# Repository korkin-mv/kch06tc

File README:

KCH06TC

This is a personal project of the controller for the control of the terrarium.

The board was developed from components available to the author, and therefore 
the project should be presented as an introduction and not in any way a 
repetition.

License: MIT.
Copyright (c) 2020 Mihail Korkin <korkin_mv@protonmail.ch>.

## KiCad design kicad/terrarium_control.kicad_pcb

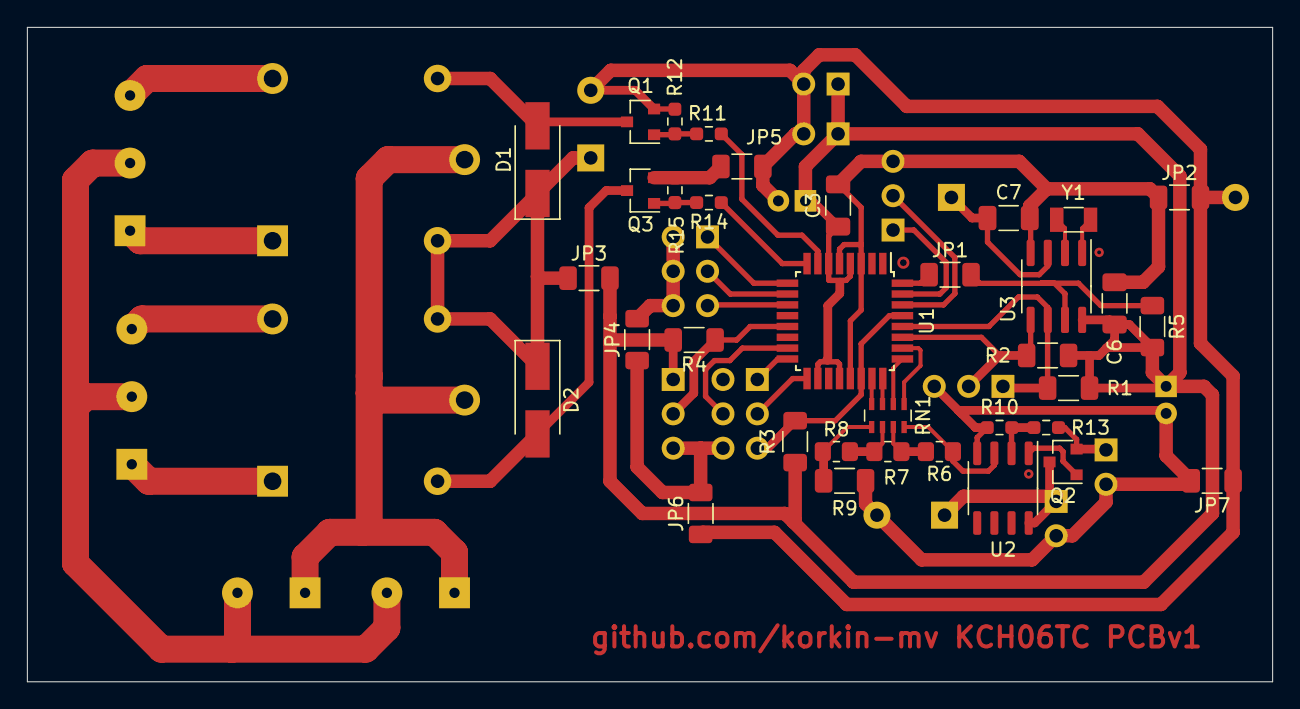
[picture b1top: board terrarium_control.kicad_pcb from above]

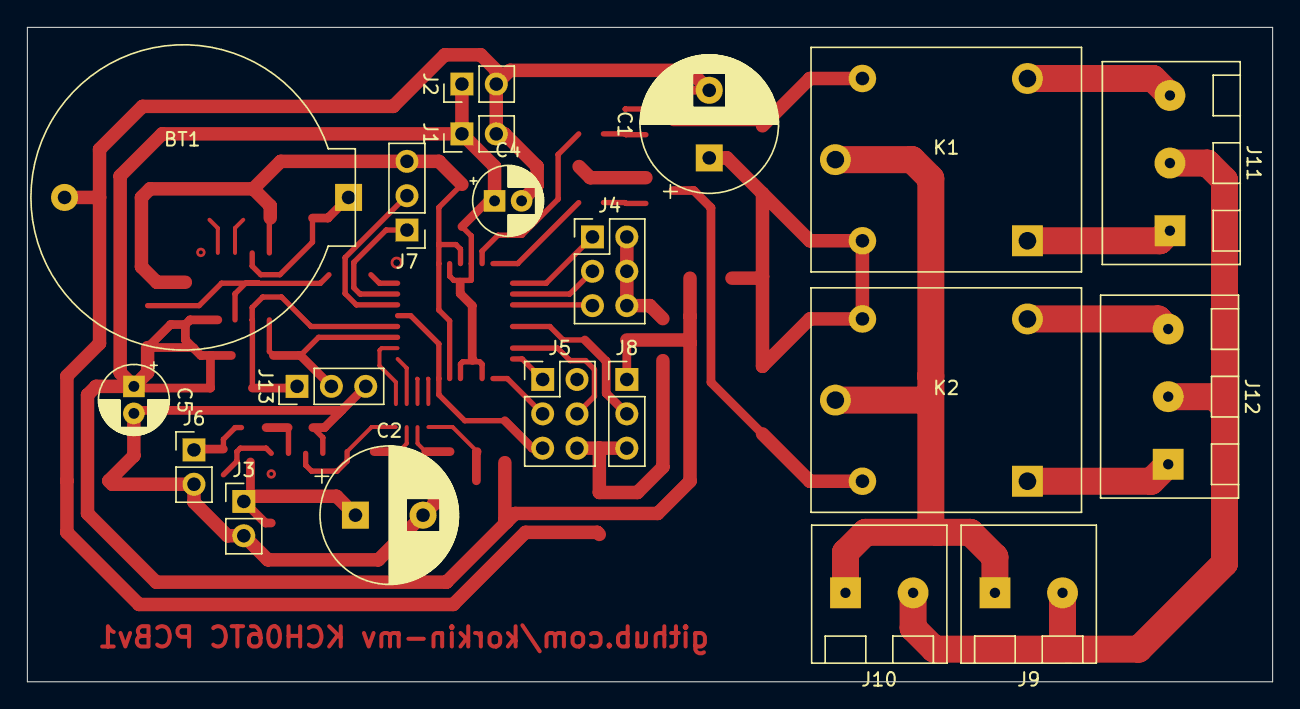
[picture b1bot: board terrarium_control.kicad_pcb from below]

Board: 2 copper layers, 92.1 x 48.4 mm, 55 parts (20 on the bottom side), 42 nets.

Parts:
BT1: CR2032; batt_holder
C1, C2: 1mF; CP_Radial_D10.0mm_P5.00mm
C3, C6: 100nF; C_1206_3216Metric_Pad1.33x1.80mm_HandSolder
C4, C5: 47uF; CP_Radial_D5.0mm_P2.00mm
C7: 10nF; C_1206_3216Metric_Pad1.33x1.80mm_HandSolder
D1, D2: M5; D_SMA_Handsoldering
J1: 5V_IN; PinHeader_1x02_P2.54mm_Vertical
J2: 5V_OUT; PinHeader_1x02_P2.54mm_Vertical
J3: 12V_IN; PinHeader_1x02_P2.54mm_Vertical
J4: SWITCHERS; PinHeader_2x03_P2.54mm_Vertical
J5: ICSP; PinHeader_2x03_P2.54mm_Vertical
J6: FUN; PinHeader_1x02_P2.54mm_Vertical
J7: UART; PinHeader_1x03_P2.54mm_Vertical
J8: ONE_WIRE; PinHeader_1x03_P2.54mm_Vertical
J9: 220V_IN; DG128-5.0-02P
J10: 220V_OUT; DG128-5.0-02P
J11: LAMP0; DG128-5.0-03P
J12: LAMP1; DG128-5.0-03P
J13: I2C; PinHeader_1x03_P2.54mm_Vertical
JP1, JP2, JP3, JP4, JP5, JP6, JP7: 0R; R_1206_3216Metric_Pad1.30x1.75mm_HandSolder
K1, K2: NRP-10-C-05D; NRP-10-C
Q1, Q3: 2N7002; SOT-23
Q2: BC817; SOT-23
R1, R2, R3, R4, R5, R9: 4.7k; R_1206_3216Metric_Pad1.30x1.75mm_HandSolder
R6, R7, R8: 2.2k; R_0805_2012Metric_Pad1.20x1.40mm_HandSolder
R10: 33k; R_0603_1608Metric_Pad0.98x0.95mm_HandSolder
R11, R14: 910; R_0603_1608Metric_Pad0.98x0.95mm_HandSolder
R12, R15: 9.1k; R_0603_1608Metric_Pad0.98x0.95mm_HandSolder
R13: 51k; R_0603_1608Metric_Pad0.98x0.95mm_HandSolder
RN1: 4.7k; R_Array_Concave_4x0603
U1: ATmega88PA-AU; TQFP-32_7x7mm_P0.8mm
U2: LM358; SO-8_3.9x4.9mm_P1.27mm
U3: DS1307Z+; SOIC-8_3.9x4.9mm_P1.27mm
Y1: 32768Hz; FC-135

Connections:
220V_N: J9.2, J10.2, J11.2, J12.2
220V_PHASE: J9.1, J10.1, K1.4, K2.4
+5V: C1.1, C3.1, C4.1, C5.1, C6.1, D1.1, D2.1, J1.1, J2.1, J8.1, JP3.1, JP3.2, K1.5, K2.3, R1.2, R2.2, R3.2, R4.2, R5.2, U1.4, U1.6, U1.18, U1.20, U3.8
+12V: C2.1, J3.1, Q2.3, U2.8
+BATT: BT1.1, C7.2, U3.3
/X+: U3.1, Y1.1
/X-: U3.2, Y1.2
DAC: R6.1, RN1.8, U2.3
DAC0: RN1.4, U1.23
DAC1: RN1.3, U1.24
DAC2: RN1.2, U1.25
DAC3: RN1.1, U1.26
ENABLE: J4.1, U1.9
FORCE0: J4.3, U1.10
FORCE1: J4.5, U1.11
FUN: J6.1, Q2.2, R13.2
GND: BT1.2, C1.2, C2.2, C3.2, C4.2, C5.2, C6.2, C7.1, J1.2, J2.2, J3.2, J4.2, J4.4, J4.6, J5.6, J6.2, J7.3, J8.3, J13.3, JP2.1, JP2.2, JP4.1, JP4.2, JP5.1, JP5.2, JP6.1, JP6.2, JP7.1, JP7.2, Q1.2, Q3.2, R9.2, R10.2, R12.1, R15.1, U1.3, U1.5, U1.21, U2.4, U3.4
MCU_RXD: J7.2, U1.30
MCU_TXD: J7.1, U1.31
MISO: J5.1, U1.16
MOSI: J5.4, U1.15
unnamed: D1.2, K1.3, Q1.3
unnamed: D2.2, K2.5, Q3.3
unnamed: J11.1, K1.1
unnamed: J11.3, K1.2
unnamed: J12.1, K2.1
unnamed: J12.3, K2.2
unnamed: Q1.1, R11.2, R12.2
unnamed: Q2.1, U2.1
unnamed: Q3.1, R14.2, R15.2
unnamed: R6.2, R7.1, RN1.7
unnamed: R7.2, R8.1, RN1.6
unnamed: R8.2, R9.1, RN1.5
unnamed: R10.1, R13.1, U2.2
ONE_WIRE: J8.2, R4.1, U1.13
RELAY0: R11.1, U1.7
RELAY1: R14.1, U1.8
RESET: J5.5, R3.1, U1.22, U1.29
SCK: J5.3, U1.17
SCL: J13.1, R1.1, U1.28, U3.6
SDA: J13.2, R2.1, U1.27, U3.5
SQW: JP1.1, JP1.2, R5.1, U1.32, U3.7

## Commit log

2020-11-28 Add scheme and datasheets
2020-11-28 Fixed missing components
2020-11-29 Assign PCB footprints to schematic symbols and add I2C connector
2020-11-29 Added elements to the board and assigned track classes
2020-11-29 Add custom battery holder
2020-11-29 ~50% of board layout completed
2020-11-30 Fix pin assigns for input switchers
2020-11-30 Board layout completed
2020-11-30 Add project name and github qrcode on pcb
2020-11-30 Remove mask from 220V traces
2020-12-05 Work on bugs: Remove QR-code; Change track distance to 0.24 mm; Add plain ground tracks instead of filler zone.
2020-12-11 Board changed from single-sided to double-sided.
2020-12-11 Rename "kicad" to "scheme"; Add license and readme.
2021-01-11 [PCB] Fix DG128 size
2021-01-13 [Firmware] Add scheme.h
2021-01-13 [Lib] Add pt-1.4
2021-01-14 [Firmware] Add queue, uart, vt and scheduler functional.
2021-01-15 [Firmware] Add one string editor
2021-01-15 [Firmware] Fix typo;
2021-01-16 [Firmware] Add minimal shell
2021-01-16 [Firmware] Refactored shell programs
2021-01-21 [Firmware] Delete C files
2021-01-21 [Lib] Add YCMOS
2021-01-21 [Firmware] Add support C++
2021-01-21 [Firmware] Add support YCMOS
